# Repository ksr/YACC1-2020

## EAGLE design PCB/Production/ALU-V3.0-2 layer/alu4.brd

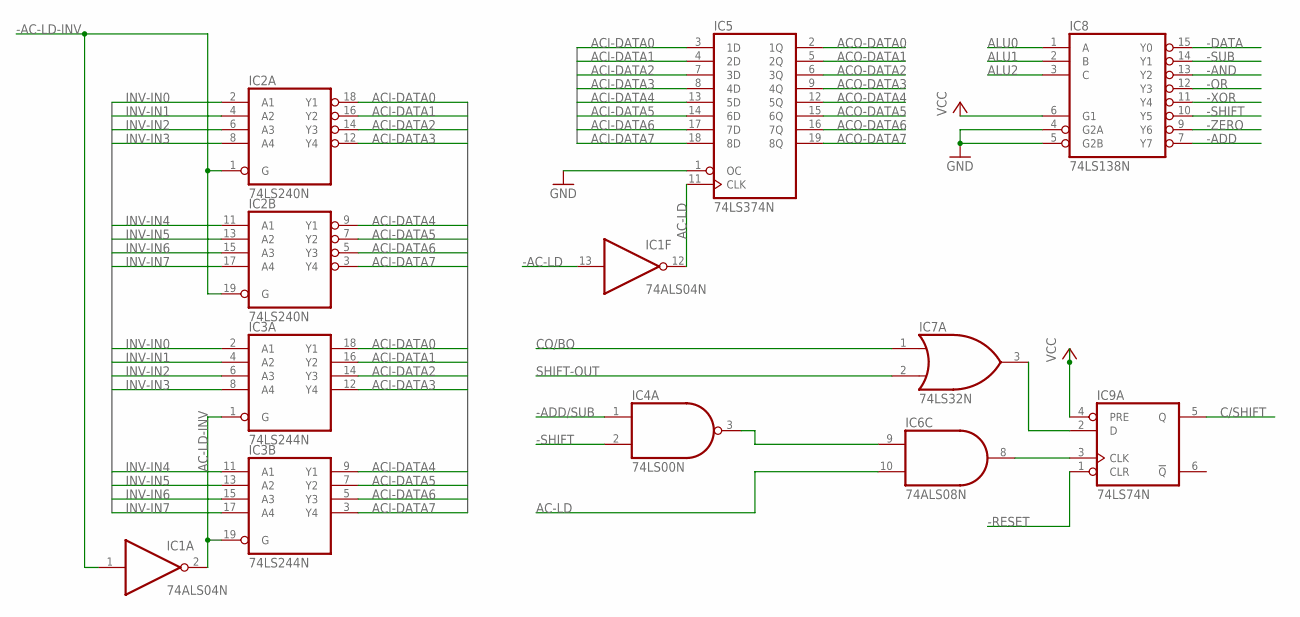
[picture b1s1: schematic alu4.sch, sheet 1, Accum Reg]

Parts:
IC1: 74ALS04N; DIL14
IC2: 74LS240N; DIL20
IC3: 74LS244N; DIL20
IC4: 74LS00N; DIL14
IC5: 74LS374N; DIL20
IC6: 74ALS08N; DIL14
IC7: 74LS32N; DIL14
IC8: 74LS138N; DIL16
IC9: 74LS74N; DIL14

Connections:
-AC-LD: IC1.13 (I); also elsewhere on the board
-AC-LD-INV: IC1.1 (I), IC2.1 (G), IC2.19 (G); also elsewhere on the board
-ADD: IC8.7 (Y7); also elsewhere on the board
-ADD/SUB: IC4.1 (I0); also elsewhere on the board
-AND: IC8.13 (Y2); also elsewhere on the board
-DATA: IC8.15 (Y0); also elsewhere on the board
-OR: IC8.12 (Y3); also elsewhere on the board
-RESET: IC9.1 (CLR); also elsewhere on the board
-SHIFT: IC4.2 (I1), IC8.10 (Y5); also elsewhere on the board
-SUB: IC8.14 (Y1); also elsewhere on the board
-XOR: IC8.11 (Y4); also elsewhere on the board
-ZERO: IC8.9 (Y6); also elsewhere on the board
AC-LD: IC1.12 (O), IC5.11 (CLK), IC6.10 (I1)
AC-LD-INV: IC1.2 (O), IC3.1 (G), IC3.19 (G); also elsewhere on the board
ACI-DATA0: IC2.18 (Y1), IC3.18 (Y1), IC5.3 (1D)
ACI-DATA1: IC2.16 (Y2), IC3.16 (Y2), IC5.4 (2D)
ACI-DATA2: IC2.14 (Y3), IC3.14 (Y3), IC5.7 (3D)
ACI-DATA3: IC2.12 (Y4), IC3.12 (Y4), IC5.8 (4D)
ACI-DATA4: IC2.9 (Y1), IC3.9 (Y1), IC5.13 (5D)
ACI-DATA5: IC2.7 (Y2), IC3.7 (Y2), IC5.14 (6D)
ACI-DATA6: IC2.5 (Y3), IC3.5 (Y3), IC5.17 (7D)
ACI-DATA7: IC2.3 (Y4), IC3.3 (Y4), IC5.18 (8D)
ACO-DATA0: IC5.2 (1Q); also elsewhere on the board
ACO-DATA1: IC5.5 (2Q); also elsewhere on the board
ACO-DATA2: IC5.6 (3Q); also elsewhere on the board
ACO-DATA3: IC5.9 (4Q); also elsewhere on the board
ACO-DATA4: IC5.12 (5Q); also elsewhere on the board
ACO-DATA5: IC5.15 (6Q); also elsewhere on the board
ACO-DATA6: IC5.16 (7Q); also elsewhere on the board
ACO-DATA7: IC5.19 (8Q); also elsewhere on the board
ALU0: IC8.1 (A); also elsewhere on the board
ALU1: IC8.2 (B); also elsewhere on the board
ALU2: IC8.3 (C); also elsewhere on the board
C/SHIFT: IC9.5 (Q); also elsewhere on the board
CO/BO: IC7.1 (I0); also elsewhere on the board
GND: IC1.7 (GND), IC2.10 (GND), IC3.10 (GND), IC4.7 (GND), IC5.1 (OC), IC5.10 (GND), IC6.7 (GND), IC7.7 (GND), IC8.4 (G2A), IC8.5 (G2B), IC8.8 (GND), IC9.7 (GND); also elsewhere on the board
INV-IN0: IC2.2 (A1), IC3.2 (A1); also elsewhere on the board
INV-IN1: IC2.4 (A2), IC3.4 (A2); also elsewhere on the board
INV-IN2: IC2.6 (A3), IC3.6 (A3); also elsewhere on the board
INV-IN3: IC2.8 (A4), IC3.8 (A4); also elsewhere on the board
INV-IN4: IC2.11 (A1), IC3.11 (A1); also elsewhere on the board
INV-IN5: IC2.13 (A2), IC3.13 (A2); also elsewhere on the board
INV-IN6: IC2.15 (A3), IC3.15 (A3); also elsewhere on the board
INV-IN7: IC2.17 (A4), IC3.17 (A4); also elsewhere on the board
unnamed: IC4.3 (O), IC6.9 (I0)
unnamed: IC6.8 (O), IC9.3 (CLK)
unnamed: IC7.3 (O), IC9.2 (D)
SHIFT-OUT: IC7.2 (I1); also elsewhere on the board
VCC: IC1.14 (VCC), IC2.20 (VCC), IC3.20 (VCC), IC4.14 (VCC), IC5.20 (VCC), IC6.14 (VCC), IC7.14 (VCC), IC8.6 (G1), IC8.16 (VCC), IC9.4 (PRE), IC9.14 (VCC); also elsewhere on the board

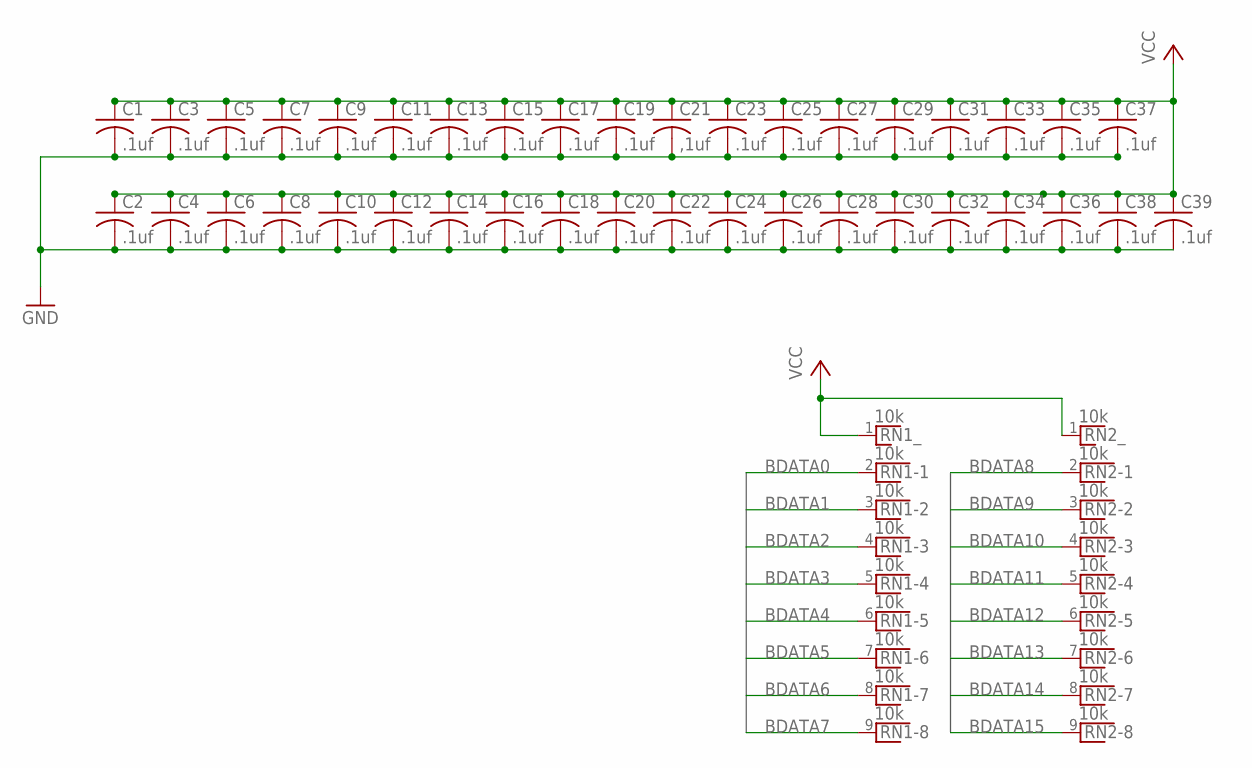
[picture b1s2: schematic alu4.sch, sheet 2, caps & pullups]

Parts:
C1, C2, C3, C4, C5, C6, C7, C8, C9, C10, C11, C12, C13, C14, C15, C16, C17, C18, C19, C20, C22, C23, C24, C25, C26, C27, C28, C29, C30, C31, C32, C33, C34, C35, C36, C37, C38, C39: .1uf; C025-024X044
C21: ,1uf; C025-024X044
RN1, RN2: 10k; RN-9

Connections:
BDATA0: RN1.2; also elsewhere on the board
BDATA1: RN1.3; also elsewhere on the board
BDATA2: RN1.4; also elsewhere on the board
BDATA3: RN1.5; also elsewhere on the board
BDATA4: RN1.6; also elsewhere on the board
BDATA5: RN1.7; also elsewhere on the board
BDATA6: RN1.8; also elsewhere on the board
BDATA7: RN1.9; also elsewhere on the board
BDATA8: RN2.2; also elsewhere on the board
BDATA9: RN2.3; also elsewhere on the board
BDATA10: RN2.4; also elsewhere on the board
BDATA11: RN2.5; also elsewhere on the board
BDATA12: RN2.6; also elsewhere on the board
BDATA13: RN2.7; also elsewhere on the board
BDATA14: RN2.8; also elsewhere on the board
BDATA15: RN2.9; also elsewhere on the board
GND: C1.2, C2.2, C3.2, C4.2, C5.2, C6.2, C7.2, C8.2, C9.2, C10.2, C11.2, C12.2, C13.2, C14.2, C15.2, C16.2, C17.2, C18.2, C19.2, C20.2, C21.2, C22.2, C23.2, C24.2, C25.2, C26.2, C27.2, C28.2, C29.2, C30.2, C31.2, C32.2, C33.2, C34.2, C35.2, C36.2, C37.2, C38.2, C39.2; also elsewhere on the board
VCC: C1.1, C2.1, C3.1, C4.1, C5.1, C6.1, C7.1, C8.1, C9.1, C10.1, C11.1, C12.1, C13.1, C14.1, C15.1, C16.1, C17.1, C18.1, C19.1, C20.1, C21.1, C22.1, C23.1, C24.1, C25.1, C26.1, C27.1, C28.1, C29.1, C30.1, C31.1, C32.1, C33.1, C34.1, C35.1, C36.1, C37.1, C38.1, C39.1, RN1.1, RN2.1; also elsewhere on the board

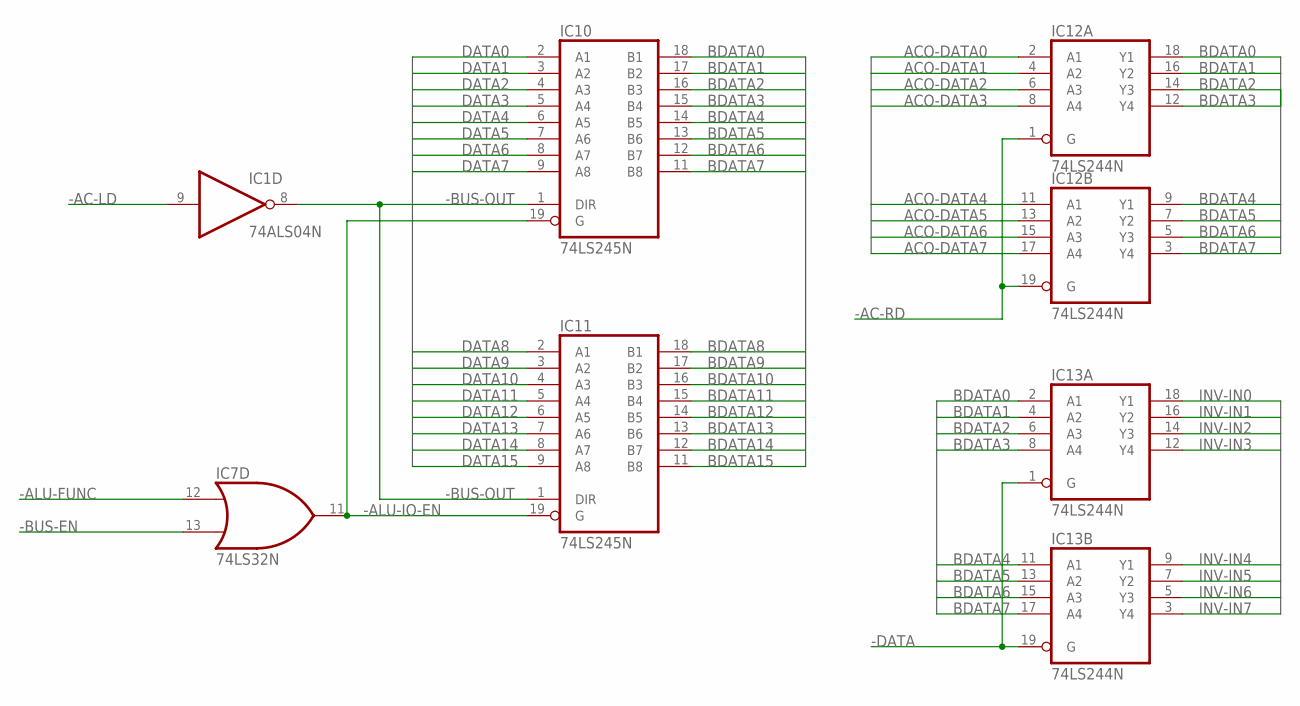
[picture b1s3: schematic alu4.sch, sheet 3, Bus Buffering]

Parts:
IC1: 74ALS04N; DIL14
IC7: 74LS32N; DIL14
IC10, IC11: 74LS245N; DIL20
IC12, IC13: 74LS244N; DIL20

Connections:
-AC-LD: IC1.9 (I); also elsewhere on the board
-AC-RD: IC12.1 (G), IC12.19 (G); also elsewhere on the board
-ALU-FUNC: IC7.12 (I0); also elsewhere on the board
-ALU-IO-EN: IC7.11 (O), IC10.19 (G), IC11.19 (G)
-BUS-EN: IC7.13 (I1); also elsewhere on the board
-BUS-OUT: IC1.8 (O), IC10.1 (DIR), IC11.1 (DIR)
-DATA: IC13.1 (G), IC13.19 (G); also elsewhere on the board
ACO-DATA0: IC12.2 (A1); also elsewhere on the board
ACO-DATA1: IC12.4 (A2); also elsewhere on the board
ACO-DATA2: IC12.6 (A3); also elsewhere on the board
ACO-DATA3: IC12.8 (A4); also elsewhere on the board
ACO-DATA4: IC12.11 (A1); also elsewhere on the board
ACO-DATA5: IC12.13 (A2); also elsewhere on the board
ACO-DATA6: IC12.15 (A3); also elsewhere on the board
ACO-DATA7: IC12.17 (A4); also elsewhere on the board
BDATA0: IC10.18 (B1), IC12.18 (Y1), IC13.2 (A1); also elsewhere on the board
BDATA1: IC10.17 (B2), IC12.16 (Y2), IC13.4 (A2); also elsewhere on the board
BDATA2: IC10.16 (B3), IC12.14 (Y3), IC13.6 (A3); also elsewhere on the board
BDATA3: IC10.15 (B4), IC12.12 (Y4), IC13.8 (A4); also elsewhere on the board
BDATA4: IC10.14 (B5), IC12.9 (Y1), IC13.11 (A1); also elsewhere on the board
BDATA5: IC10.13 (B6), IC12.7 (Y2), IC13.13 (A2); also elsewhere on the board
BDATA6: IC10.12 (B7), IC12.5 (Y3), IC13.15 (A3); also elsewhere on the board
BDATA7: IC10.11 (B8), IC12.3 (Y4), IC13.17 (A4); also elsewhere on the board
BDATA8: IC11.18 (B1); also elsewhere on the board
BDATA9: IC11.17 (B2); also elsewhere on the board
BDATA10: IC11.16 (B3); also elsewhere on the board
BDATA11: IC11.15 (B4); also elsewhere on the board
BDATA12: IC11.14 (B5); also elsewhere on the board
BDATA13: IC11.13 (B6); also elsewhere on the board
BDATA14: IC11.12 (B7); also elsewhere on the board
BDATA15: IC11.11 (B8); also elsewhere on the board
DATA0: IC10.2 (A1); also elsewhere on the board
DATA1: IC10.3 (A2); also elsewhere on the board
DATA2: IC10.4 (A3); also elsewhere on the board
DATA3: IC10.5 (A4); also elsewhere on the board
DATA4: IC10.6 (A5); also elsewhere on the board
DATA5: IC10.7 (A6); also elsewhere on the board
DATA6: IC10.8 (A7); also elsewhere on the board
DATA7: IC10.9 (A8); also elsewhere on the board
DATA8: IC11.2 (A1); also elsewhere on the board
DATA9: IC11.3 (A2); also elsewhere on the board
DATA10: IC11.4 (A3); also elsewhere on the board
DATA11: IC11.5 (A4); also elsewhere on the board
DATA12: IC11.6 (A5); also elsewhere on the board
DATA13: IC11.7 (A6); also elsewhere on the board
DATA14: IC11.8 (A7); also elsewhere on the board
DATA15: IC11.9 (A8); also elsewhere on the board
GND: IC1.7 (GND), IC7.7 (GND), IC10.10 (GND), IC11.10 (GND), IC12.10 (GND), IC13.10 (GND); also elsewhere on the board
INV-IN0: IC13.18 (Y1); also elsewhere on the board
INV-IN1: IC13.16 (Y2); also elsewhere on the board
INV-IN2: IC13.14 (Y3); also elsewhere on the board
INV-IN3: IC13.12 (Y4); also elsewhere on the board
INV-IN4: IC13.9 (Y1); also elsewhere on the board
INV-IN5: IC13.7 (Y2); also elsewhere on the board
INV-IN6: IC13.5 (Y3); also elsewhere on the board
INV-IN7: IC13.3 (Y4); also elsewhere on the board
VCC: IC1.14 (VCC), IC7.14 (VCC), IC10.20 (VCC), IC11.20 (VCC), IC12.20 (VCC), IC13.20 (VCC); also elsewhere on the board

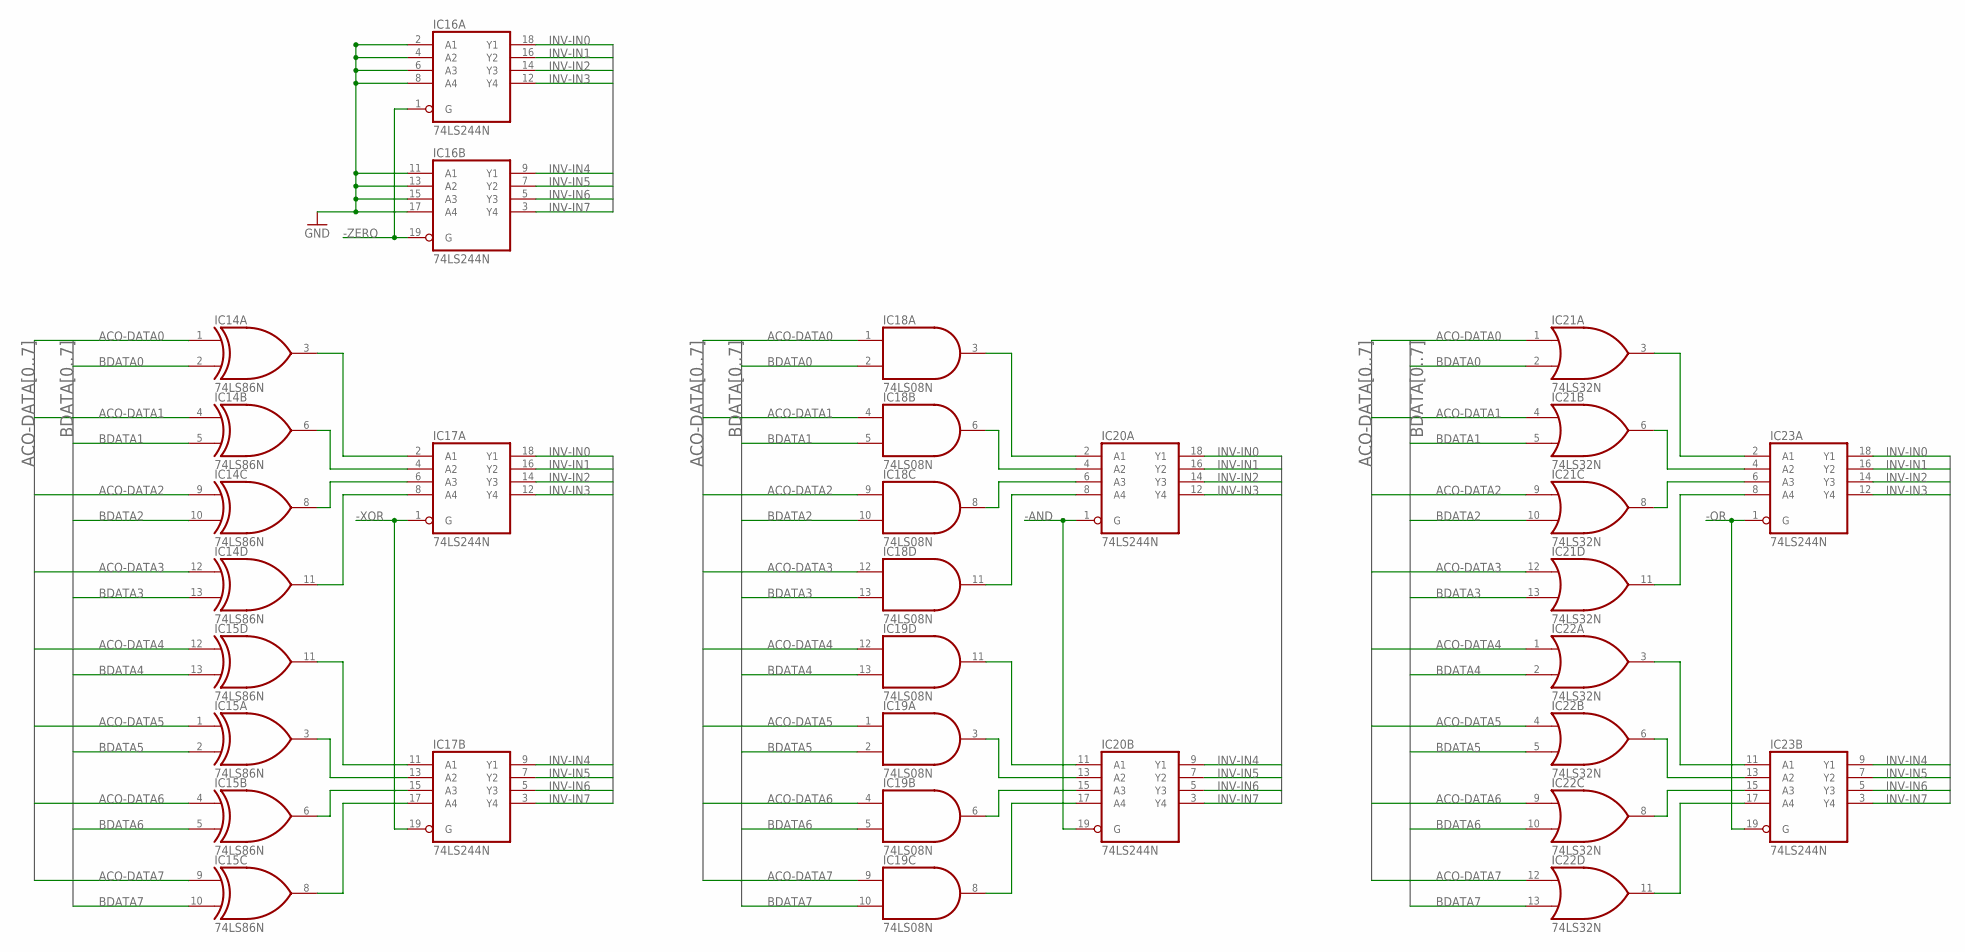
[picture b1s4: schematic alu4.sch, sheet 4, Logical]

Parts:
IC14, IC15: 74LS86N; DIL14
IC16, IC17, IC20, IC23: 74LS244N; DIL20
IC18, IC19: 74LS08N; DIL14
IC21, IC22: 74LS32N; DIL14

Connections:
-AND: IC20.1 (G), IC20.19 (G); also elsewhere on the board
-OR: IC23.1 (G), IC23.19 (G); also elsewhere on the board
-XOR: IC17.1 (G), IC17.19 (G); also elsewhere on the board
-ZERO: IC16.1 (G), IC16.19 (G); also elsewhere on the board
ACO-DATA0: IC14.1 (I0), IC18.1 (I0), IC21.1 (I0); also elsewhere on the board
ACO-DATA1: IC14.4 (I0), IC18.4 (I0), IC21.4 (I0); also elsewhere on the board
ACO-DATA2: IC14.9 (I0), IC18.9 (I0), IC21.9 (I0); also elsewhere on the board
ACO-DATA3: IC14.12 (I0), IC18.12 (I0), IC21.12 (I0); also elsewhere on the board
ACO-DATA4: IC15.12 (I0), IC19.12 (I0), IC22.1 (I0); also elsewhere on the board
ACO-DATA5: IC15.1 (I0), IC19.1 (I0), IC22.4 (I0); also elsewhere on the board
ACO-DATA6: IC15.4 (I0), IC19.4 (I0), IC22.9 (I0); also elsewhere on the board
ACO-DATA7: IC15.9 (I0), IC19.9 (I0), IC22.12 (I0); also elsewhere on the board
BDATA0: IC14.2 (I1), IC18.2 (I1), IC21.2 (I1); also elsewhere on the board
BDATA1: IC14.5 (I1), IC18.5 (I1), IC21.5 (I1); also elsewhere on the board
BDATA2: IC14.10 (I1), IC18.10 (I1), IC21.10 (I1); also elsewhere on the board
BDATA3: IC14.13 (I1), IC18.13 (I1), IC21.13 (I1); also elsewhere on the board
BDATA4: IC15.13 (I1), IC19.13 (I1), IC22.2 (I1); also elsewhere on the board
BDATA5: IC15.2 (I1), IC19.2 (I1), IC22.5 (I1); also elsewhere on the board
BDATA6: IC15.5 (I1), IC19.5 (I1), IC22.10 (I1); also elsewhere on the board
BDATA7: IC15.10 (I1), IC19.10 (I1), IC22.13 (I1); also elsewhere on the board
GND: IC14.7 (GND), IC15.7 (GND), IC16.2 (A1), IC16.4 (A2), IC16.6 (A3), IC16.8 (A4), IC16.10 (GND), IC16.11 (A1), IC16.13 (A2), IC16.15 (A3), IC16.17 (A4), IC17.10 (GND), IC18.7 (GND), IC19.7 (GND), IC20.10 (GND), IC21.7 (GND), IC22.7 (GND), IC23.10 (GND); also elsewhere on the board
INV-IN0: IC16.18 (Y1), IC17.18 (Y1), IC20.18 (Y1), IC23.18 (Y1); also elsewhere on the board
INV-IN1: IC16.16 (Y2), IC17.16 (Y2), IC20.16 (Y2), IC23.16 (Y2); also elsewhere on the board
INV-IN2: IC16.14 (Y3), IC17.14 (Y3), IC20.14 (Y3), IC23.14 (Y3); also elsewhere on the board
INV-IN3: IC16.12 (Y4), IC17.12 (Y4), IC20.12 (Y4), IC23.12 (Y4); also elsewhere on the board
INV-IN4: IC16.9 (Y1), IC17.9 (Y1), IC20.9 (Y1), IC23.9 (Y1); also elsewhere on the board
INV-IN5: IC16.7 (Y2), IC17.7 (Y2), IC20.7 (Y2), IC23.7 (Y2); also elsewhere on the board
INV-IN6: IC16.5 (Y3), IC17.5 (Y3), IC20.5 (Y3), IC23.5 (Y3); also elsewhere on the board
INV-IN7: IC16.3 (Y4), IC17.3 (Y4), IC20.3 (Y4), IC23.3 (Y4); also elsewhere on the board
unnamed: IC21.3 (O), IC23.2 (A1)
unnamed: IC21.6 (O), IC23.4 (A2)
unnamed: IC21.8 (O), IC23.6 (A3)
unnamed: IC21.11 (O), IC23.8 (A4)
unnamed: IC22.3 (O), IC23.11 (A1)
unnamed: IC22.6 (O), IC23.13 (A2)
unnamed: IC22.8 (O), IC23.15 (A3)
unnamed: IC22.11 (O), IC23.17 (A4)
unnamed: IC18.3 (O), IC20.2 (A1)
unnamed: IC18.6 (O), IC20.4 (A2)
unnamed: IC18.8 (O), IC20.6 (A3)
unnamed: IC18.11 (O), IC20.8 (A4)
unnamed: IC19.11 (O), IC20.11 (A1)
unnamed: IC19.3 (O), IC20.13 (A2)
unnamed: IC19.6 (O), IC20.15 (A3)
unnamed: IC19.8 (O), IC20.17 (A4)
unnamed: IC14.3 (O), IC17.2 (A1)
unnamed: IC14.6 (O), IC17.4 (A2)
unnamed: IC14.8 (O), IC17.6 (A3)
unnamed: IC14.11 (O), IC17.8 (A4)
unnamed: IC15.11 (O), IC17.11 (A1)
unnamed: IC15.3 (O), IC17.13 (A2)
unnamed: IC15.6 (O), IC17.15 (A3)
unnamed: IC15.8 (O), IC17.17 (A4)
VCC: IC14.14 (VCC), IC15.14 (VCC), IC16.20 (VCC), IC17.20 (VCC), IC18.14 (VCC), IC19.14 (VCC), IC20.20 (VCC), IC21.14 (VCC), IC22.14 (VCC), IC23.20 (VCC); also elsewhere on the board

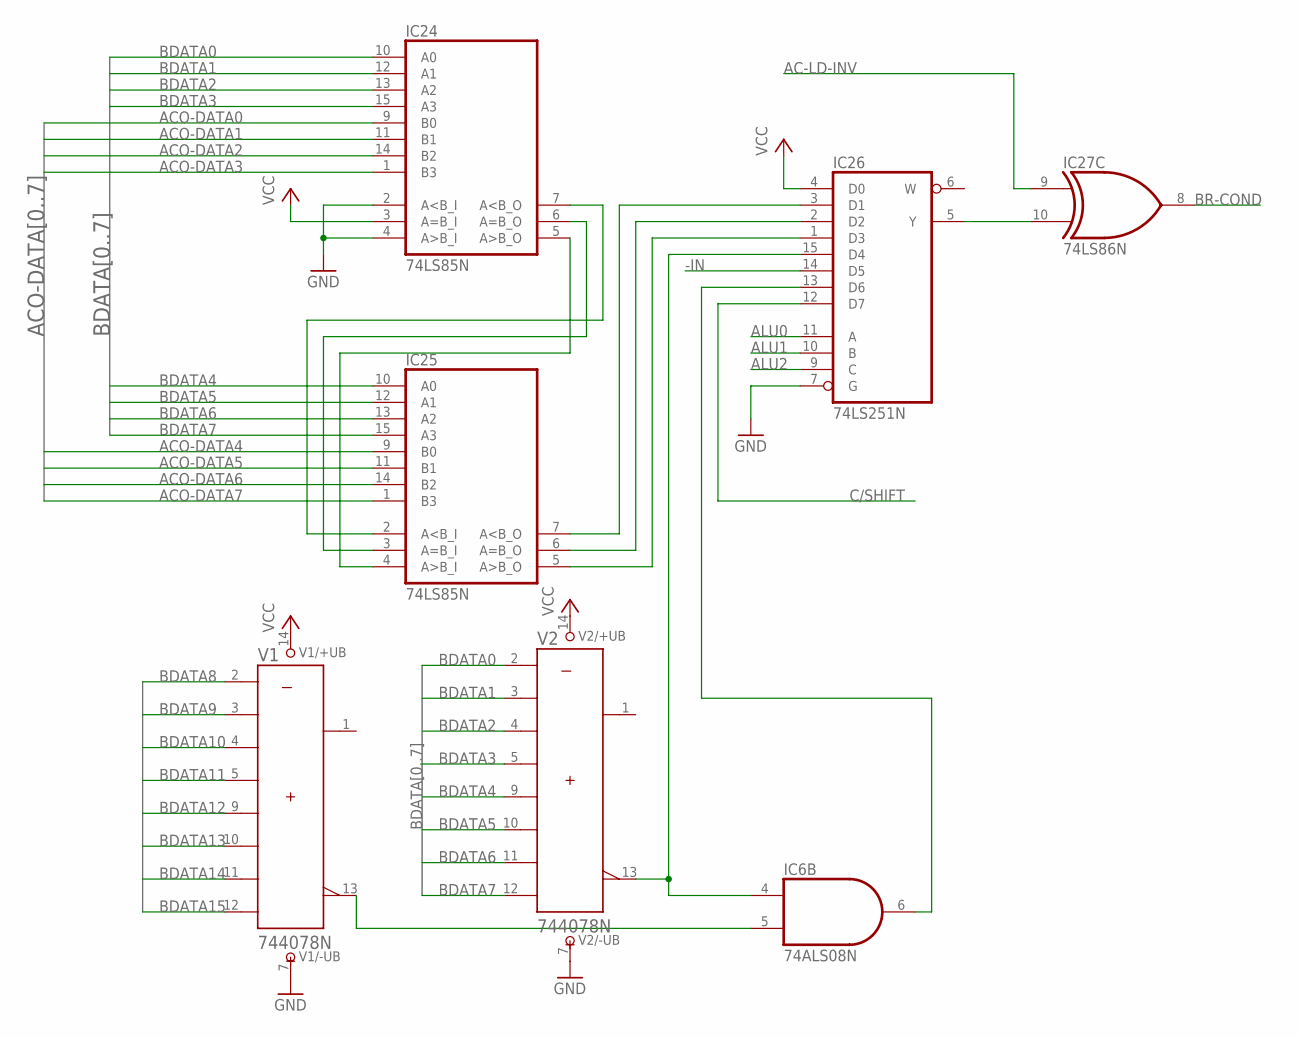
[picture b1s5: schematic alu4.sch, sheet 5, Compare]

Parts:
IC6: 74ALS08N; DIL14
IC24, IC25: 74LS85N; DIL16
IC26: 74LS251N; DIL16
IC27: 74LS86N; DIL14
V1, V2: 744078N; DIL14

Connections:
-IN: IC26.14 (D5); also elsewhere on the board
AC-LD-INV: IC27.9 (I0); also elsewhere on the board
ACO-DATA0: IC24.9 (B0); also elsewhere on the board
ACO-DATA1: IC24.11 (B1); also elsewhere on the board
ACO-DATA2: IC24.14 (B2); also elsewhere on the board
ACO-DATA3: IC24.1 (B3); also elsewhere on the board
ACO-DATA4: IC25.9 (B0); also elsewhere on the board
ACO-DATA5: IC25.11 (B1); also elsewhere on the board
ACO-DATA6: IC25.14 (B2); also elsewhere on the board
ACO-DATA7: IC25.1 (B3); also elsewhere on the board
ALU0: IC26.11 (A); also elsewhere on the board
ALU1: IC26.10 (B); also elsewhere on the board
ALU2: IC26.9 (C); also elsewhere on the board
BDATA0: IC24.10 (A0), V2.2 (A); also elsewhere on the board
BDATA1: IC24.12 (A1), V2.3 (B); also elsewhere on the board
BDATA2: IC24.13 (A2), V2.4 (C); also elsewhere on the board
BDATA3: IC24.15 (A3), V2.5 (D); also elsewhere on the board
BDATA4: IC25.10 (A0), V2.9 (E); also elsewhere on the board
BDATA5: IC25.12 (A1), V2.10 (F); also elsewhere on the board
BDATA6: IC25.13 (A2), V2.11 (G); also elsewhere on the board
BDATA7: IC25.15 (A3), V2.12 (H); also elsewhere on the board
BDATA8: V1.2 (A); also elsewhere on the board
BDATA9: V1.3 (B); also elsewhere on the board
BDATA10: V1.4 (C); also elsewhere on the board
BDATA11: V1.5 (D); also elsewhere on the board
BDATA12: V1.9 (E); also elsewhere on the board
BDATA13: V1.10 (F); also elsewhere on the board
BDATA14: V1.11 (G); also elsewhere on the board
BDATA15: V1.12 (H); also elsewhere on the board
BR-COND: IC27.8 (O); also elsewhere on the board
C/SHIFT: IC26.12 (D7); also elsewhere on the board
GND: IC6.7 (GND), IC24.2 (A<B_I), IC24.4 (A>B_I), IC24.8 (GND), IC25.8 (GND), IC26.7 (G), IC26.8 (GND), IC27.7 (GND), V1.7 (-UB), V2.7 (-UB); also elsewhere on the board
unnamed: IC6.4 (I0), IC26.15 (D4), V2.13 (W)
unnamed: IC24.5 (A>B_O), IC25.4 (A>B_I)
unnamed: IC24.6 (A=B_O), IC25.3 (A=B_I)
unnamed: IC24.7 (A<B_O), IC25.2 (A<B_I)
unnamed: IC25.7 (A<B_O), IC26.3 (D1)
unnamed: IC25.6 (A=B_O), IC26.2 (D2)
unnamed: IC25.5 (A>B_O), IC26.1 (D3)
unnamed: IC6.5 (I1), V1.13 (W)
unnamed: IC6.6 (O), IC26.13 (D6)
unnamed: IC26.5 (Y), IC27.10 (I1)
VCC: IC6.14 (VCC), IC24.3 (A=B_I), IC24.16 (VCC), IC25.16 (VCC), IC26.4 (D0), IC26.16 (VCC), IC27.14 (VCC), V1.14 (+UB), V2.14 (+UB); also elsewhere on the board

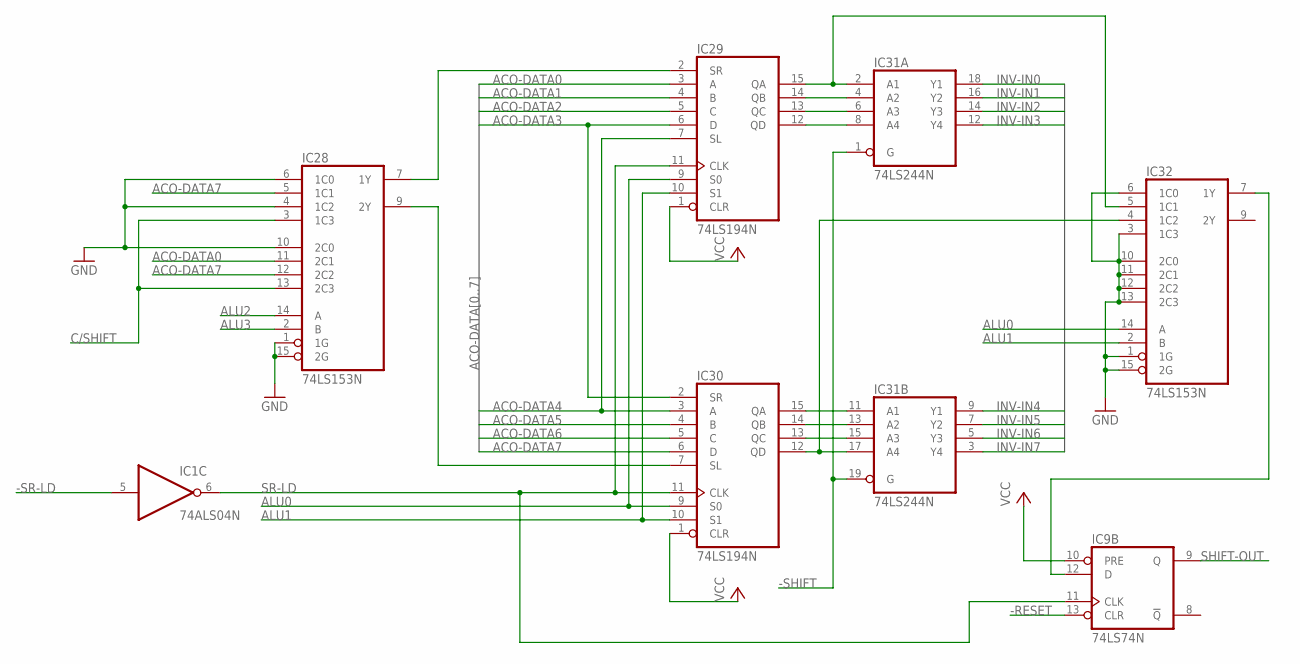
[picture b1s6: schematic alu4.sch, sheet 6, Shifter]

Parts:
IC1: 74ALS04N; DIL14
IC9: 74LS74N; DIL14
IC28, IC32: 74LS153N; DIL16
IC29, IC30: 74LS194N; DIL16
IC31: 74LS244N; DIL20

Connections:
-RESET: IC9.13 (CLR); also elsewhere on the board
-SHIFT: IC31.1 (G), IC31.19 (G); also elsewhere on the board
-SR-LD: IC1.5 (I); also elsewhere on the board
ACO-DATA0: IC28.11 (2C1), IC29.3 (A); also elsewhere on the board
ACO-DATA1: IC29.4 (B); also elsewhere on the board
ACO-DATA2: IC29.5 (C); also elsewhere on the board
ACO-DATA3: IC29.6 (D), IC30.2 (SR); also elsewhere on the board
ACO-DATA4: IC29.7 (SL), IC30.3 (A); also elsewhere on the board
ACO-DATA5: IC30.4 (B); also elsewhere on the board
ACO-DATA6: IC30.5 (C); also elsewhere on the board
ACO-DATA7: IC28.5 (1C1), IC28.12 (2C2), IC30.6 (D); also elsewhere on the board
ALU0: IC29.9 (S0), IC30.9 (S0), IC32.14 (A); also elsewhere on the board
ALU1: IC29.10 (S1), IC30.10 (S1), IC32.2 (B); also elsewhere on the board
ALU2: IC28.14 (A); also elsewhere on the board
ALU3: IC28.2 (B); also elsewhere on the board
C/SHIFT: IC28.3 (1C3), IC28.13 (2C3); also elsewhere on the board
GND: IC1.7 (GND), IC9.7 (GND), IC28.1 (1G), IC28.4 (1C2), IC28.6 (1C0), IC28.8 (GND), IC28.10 (2C0), IC28.15 (2G), IC29.8 (GND), IC30.8 (GND), IC31.10 (GND), IC32.1 (1G), IC32.3 (1C3), IC32.6 (1C0), IC32.8 (GND), IC32.10 (2C0), IC32.11 (2C1), IC32.12 (2C2), IC32.13 (2C3), IC32.15 (2G); also elsewhere on the board
INV-IN0: IC31.18 (Y1); also elsewhere on the board
INV-IN1: IC31.16 (Y2); also elsewhere on the board
INV-IN2: IC31.14 (Y3); also elsewhere on the board
INV-IN3: IC31.12 (Y4); also elsewhere on the board
INV-IN4: IC31.9 (Y1); also elsewhere on the board
INV-IN5: IC31.7 (Y2); also elsewhere on the board
INV-IN6: IC31.5 (Y3); also elsewhere on the board
INV-IN7: IC31.3 (Y4); also elsewhere on the board
unnamed: IC9.12 (D), IC32.7 (1Y)
unnamed: IC29.15 (QA), IC31.2 (A1), IC32.5 (1C1)
unnamed: IC29.14 (QB), IC31.4 (A2)
unnamed: IC29.13 (QC), IC31.6 (A3)
unnamed: IC29.12 (QD), IC31.8 (A4)
unnamed: IC30.15 (QA), IC31.11 (A1)
unnamed: IC30.14 (QB), IC31.13 (A2)
unnamed: IC30.13 (QC), IC31.15 (A3)
unnamed: IC30.12 (QD), IC31.17 (A4), IC32.4 (1C2)
unnamed: IC28.7 (1Y), IC29.2 (SR)
unnamed: IC28.9 (2Y), IC30.7 (SL)
SHIFT-OUT: IC9.9 (Q); also elsewhere on the board
SR-LD: IC1.6 (O), IC9.11 (CLK), IC29.11 (CLK), IC30.11 (CLK)
VCC: IC1.14 (VCC), IC9.10 (PRE), IC9.14 (VCC), IC28.16 (VCC), IC29.1 (CLR), IC29.16 (VCC), IC30.1 (CLR), IC30.16 (VCC), IC31.20 (VCC), IC32.16 (VCC); also elsewhere on the board

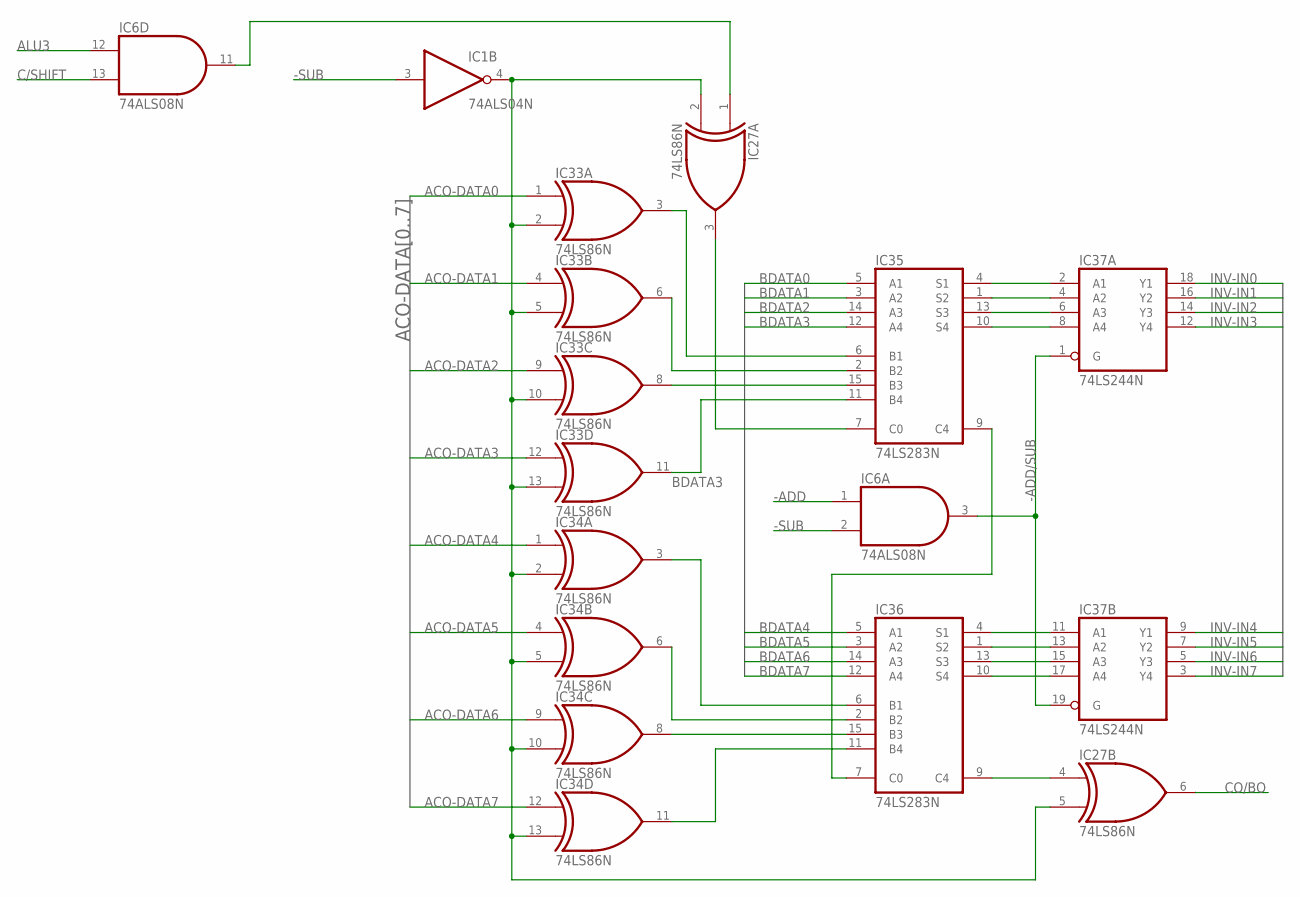
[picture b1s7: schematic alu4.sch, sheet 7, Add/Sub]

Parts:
IC1: 74ALS04N; DIL14
IC6: 74ALS08N; DIL14
IC27, IC33, IC34: 74LS86N; DIL14
IC35, IC36: 74LS283N; DIL16
IC37: 74LS244N; DIL20

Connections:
-ADD: IC6.1 (I0); also elsewhere on the board
-ADD/SUB: IC6.3 (O), IC37.1 (G), IC37.19 (G); also elsewhere on the board
-SUB: IC1.3 (I), IC6.2 (I1); also elsewhere on the board
ACO-DATA0: IC33.1 (I0); also elsewhere on the board
ACO-DATA1: IC33.4 (I0); also elsewhere on the board
ACO-DATA2: IC33.9 (I0); also elsewhere on the board
ACO-DATA3: IC33.12 (I0); also elsewhere on the board
ACO-DATA4: IC34.1 (I0); also elsewhere on the board
ACO-DATA5: IC34.4 (I0); also elsewhere on the board
ACO-DATA6: IC34.9 (I0); also elsewhere on the board
ACO-DATA7: IC34.12 (I0); also elsewhere on the board
ALU3: IC6.12 (I0); also elsewhere on the board
BDATA0: IC35.5 (A1); also elsewhere on the board
BDATA1: IC35.3 (A2); also elsewhere on the board
BDATA2: IC35.14 (A3); also elsewhere on the board
BDATA3: IC35.12 (A4); also elsewhere on the board
BDATA4: IC36.5 (A1); also elsewhere on the board
BDATA5: IC36.3 (A2); also elsewhere on the board
BDATA6: IC36.14 (A3); also elsewhere on the board
BDATA7: IC36.12 (A4); also elsewhere on the board
C/SHIFT: IC6.13 (I1); also elsewhere on the board
CO/BO: IC27.6 (O); also elsewhere on the board
GND: IC1.7 (GND), IC6.7 (GND), IC27.7 (GND), IC33.7 (GND), IC34.7 (GND), IC35.8 (GND), IC36.8 (GND), IC37.10 (GND); also elsewhere on the board
INV-IN0: IC37.18 (Y1); also elsewhere on the board
INV-IN1: IC37.16 (Y2); also elsewhere on the board
INV-IN2: IC37.14 (Y3); also elsewhere on the board
INV-IN3: IC37.12 (Y4); also elsewhere on the board
INV-IN4: IC37.9 (Y1); also elsewhere on the board
INV-IN5: IC37.7 (Y2); also elsewhere on the board
INV-IN6: IC37.5 (Y3); also elsewhere on the board
INV-IN7: IC37.3 (Y4); also elsewhere on the board
unnamed: IC27.4 (I0), IC36.9 (C4)
unnamed: IC27.3 (O), IC35.7 (C0)
unnamed: IC6.11 (O), IC27.1 (I0)
unnamed: IC33.6 (O), IC35.2 (B2)
unnamed: IC34.6 (O), IC36.2 (B2)
unnamed: IC33.8 (O), IC35.15 (B3)
unnamed: IC33.11 (O), IC35.11 (B4)
unnamed: IC33.3 (O), IC35.6 (B1)
unnamed: IC34.3 (O), IC36.6 (B1)
unnamed: IC34.8 (O), IC36.15 (B3)
unnamed: IC34.11 (O), IC36.11 (B4)
unnamed: IC35.4 (S1), IC37.2 (A1)
unnamed: IC35.1 (S2), IC37.4 (A2)
unnamed: IC35.13 (S3), IC37.6 (A3)
unnamed: IC35.10 (S4), IC37.8 (A4)
unnamed: IC36.4 (S1), IC37.11 (A1)
unnamed: IC36.1 (S2), IC37.13 (A2)
unnamed: IC36.13 (S3), IC37.15 (A3)
unnamed: IC36.10 (S4), IC37.17 (A4)
unnamed: IC35.9 (C4), IC36.7 (C0)
SUB: IC1.4 (O), IC27.2 (I1), IC27.5 (I1), IC33.2 (I1), IC33.5 (I1), IC33.10 (I1), IC33.13 (I1), IC34.2 (I1), IC34.5 (I1), IC34.10 (I1), IC34.13 (I1)
VCC: IC1.14 (VCC), IC6.14 (VCC), IC27.14 (VCC), IC33.14 (VCC), IC34.14 (VCC), IC35.16 (VCC), IC36.16 (VCC), IC37.20 (VCC); also elsewhere on the board

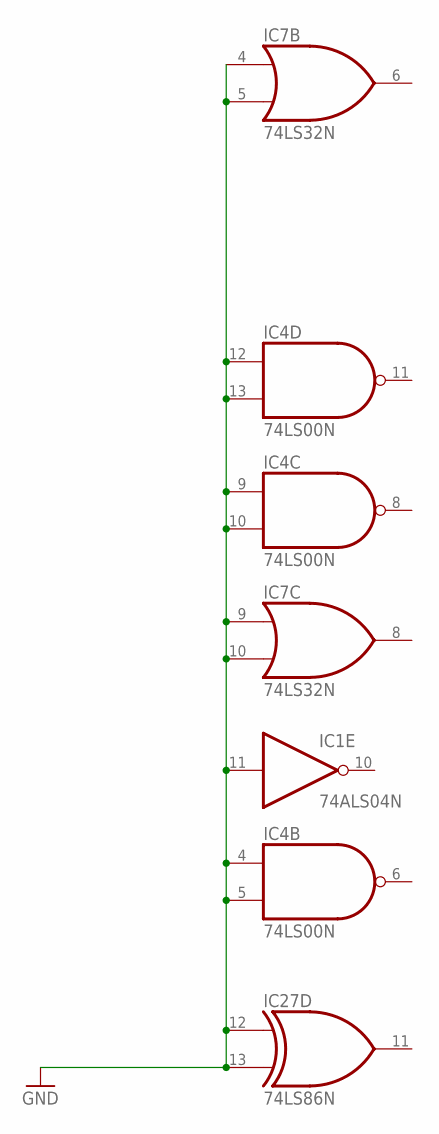
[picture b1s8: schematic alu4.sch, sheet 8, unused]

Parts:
IC1: 74ALS04N; DIL14
IC4: 74LS00N; DIL14
IC7: 74LS32N; DIL14
IC27: 74LS86N; DIL14

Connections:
GND: IC1.7 (GND), IC1.11 (I), IC4.4 (I0), IC4.5 (I1), IC4.7 (GND), IC4.9 (I0), IC4.10 (I1), IC4.12 (I0), IC4.13 (I1), IC7.4 (I0), IC7.5 (I1), IC7.7 (GND), IC7.9 (I0), IC7.10 (I1), IC27.7 (GND), IC27.12 (I0), IC27.13 (I1); also elsewhere on the board
VCC: IC1.14 (VCC), IC4.14 (VCC), IC7.14 (VCC), IC27.14 (VCC); also elsewhere on the board

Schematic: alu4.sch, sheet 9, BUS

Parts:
PWR: LED5MM
R1: 330; 0207/10
SV1: MA05-2
X1: FABC96R

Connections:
-AC-LD: X1.C22; also elsewhere on the board
-AC-LD-INV: X1.C20; also elsewhere on the board
-AC-RD: X1.C21; also elsewhere on the board
-ADDR-REG-LD0: X1.C4
-ADDR-REG-LD1: X1.C6
-ADDR-REG-RD0: X1.C3
-ADDR-REG-RD1: X1.C5
-ALU-FUNC: X1.C15; also elsewhere on the board
-BUS-EN: X1.C28; also elsewhere on the board
-HL-SWAP: X1.C25
-IN: X1.C26; also elsewhere on the board
-INT: X1.C13
-INTA: X1.C14
-IO-ADDR-LD: X1.C11
-IO-RD: X1.B25
-IO-WR: X1.B26
-MEM-RD: X1.B23
-MEM-WR: X1.B24
-OUT: X1.C27
-REG-DN: X1.B21
-REG-FUNC-LD: X1.B8
-REG-FUNC-RD: X1.B7
-REG-LD-HI: X1.B20
-REG-LD-LO: X1.B18
-REG-RD-HI: X1.B19
-REG-RD-LO: X1.B17
-REG-UP: X1.B22
-RESET: X1.C30; also elsewhere on the board
-RUN: X1.C29
-SR-LD: X1.C23; also elsewhere on the board
-TMP-REG-LD0: X1.B28
-TMP-REG-LD1: X1.B30
-TMP-REG-RD0: X1.B27
-TMP-REG-RD1: X1.B29
ACO-DATA0: SV1.1; also elsewhere on the board
ACO-DATA1: SV1.2; also elsewhere on the board
ACO-DATA2: SV1.3; also elsewhere on the board
ACO-DATA3: SV1.4; also elsewhere on the board
ACO-DATA4: SV1.5; also elsewhere on the board
ACO-DATA5: SV1.6; also elsewhere on the board
ACO-DATA6: SV1.7; also elsewhere on the board
ACO-DATA7: SV1.8; also elsewhere on the board
ADDR0: X1.A3
ADDR1: X1.A4
ADDR2: X1.A5
ADDR3: X1.A6
ADDR4: X1.A7
ADDR5: X1.A8
ADDR6: X1.A9
ADDR7: X1.A10
ADDR8: X1.A11
ADDR9: X1.A12
ADDR10: X1.A13
ADDR11: X1.A14
ADDR12: X1.A15
ADDR13: X1.A16
ADDR14: X1.A17
ADDR15: X1.A18
ALU0: X1.C16; also elsewhere on the board
ALU1: X1.C17; also elsewhere on the board
ALU2: X1.C18; also elsewhere on the board
ALU3: X1.C19; also elsewhere on the board
BR-COND: X1.C24; also elsewhere on the board
C/SHIFT: SV1.9; also elsewhere on the board
DATA0: X1.A19; also elsewhere on the board
DATA1: X1.A20; also elsewhere on the board
DATA2: X1.A21; also elsewhere on the board
DATA3: X1.A22; also elsewhere on the board
DATA4: X1.A23; also elsewhere on the board
DATA5: X1.A24; also elsewhere on the board
DATA6: X1.A25; also elsewhere on the board
DATA7: X1.A26; also elsewhere on the board
DATA8: X1.A27; also elsewhere on the board
DATA9: X1.A28; also elsewhere on the board
DATA10: X1.A29; also elsewhere on the board
DATA11: X1.A30; also elsewhere on the board
DATA12: X1.B3; also elsewhere on the board
DATA13: X1.B4; also elsewhere on the board
DATA14: X1.B5; also elsewhere on the board
DATA15: X1.B6; also elsewhere on the board
GND: PWR.K (C), SV1.10, X1.A1, X1.A32, X1.B1, X1.B32, X1.C1, X1.C32; also elsewhere on the board
IO-ADDR0: X1.C7
IO-ADDR1: X1.C8
IO-ADDR2: X1.C9
IO-ADDR3: X1.C10
unnamed: PWR.A, R1.1
REG-LD-ID0: X1.B13
REG-LD-ID1: X1.B14
REG-LD-ID2: X1.B15
REG-LD-ID3: X1.B16
REG-RD-ID0: X1.B9
REG-RD-ID1: X1.B10
REG-RD-ID2: X1.B11
REG-RD-ID3: X1.B12
UNUSED0: X1.C12
VCC: R1.2, X1.A2, X1.A31, X1.B2, X1.B31, X1.C2, X1.C31; also elsewhere on the board

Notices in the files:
parts and their libraries:
SparkFun-DigitalIC: Licensing: CC v3.0 Share-Alike You are welcome to use this library for commercial purposes.
SparkFun-Connectors: Licensing: Creative Commons ShareAlike 4.0 International - https://creativecommons.org/licenses/by-sa/4.0
